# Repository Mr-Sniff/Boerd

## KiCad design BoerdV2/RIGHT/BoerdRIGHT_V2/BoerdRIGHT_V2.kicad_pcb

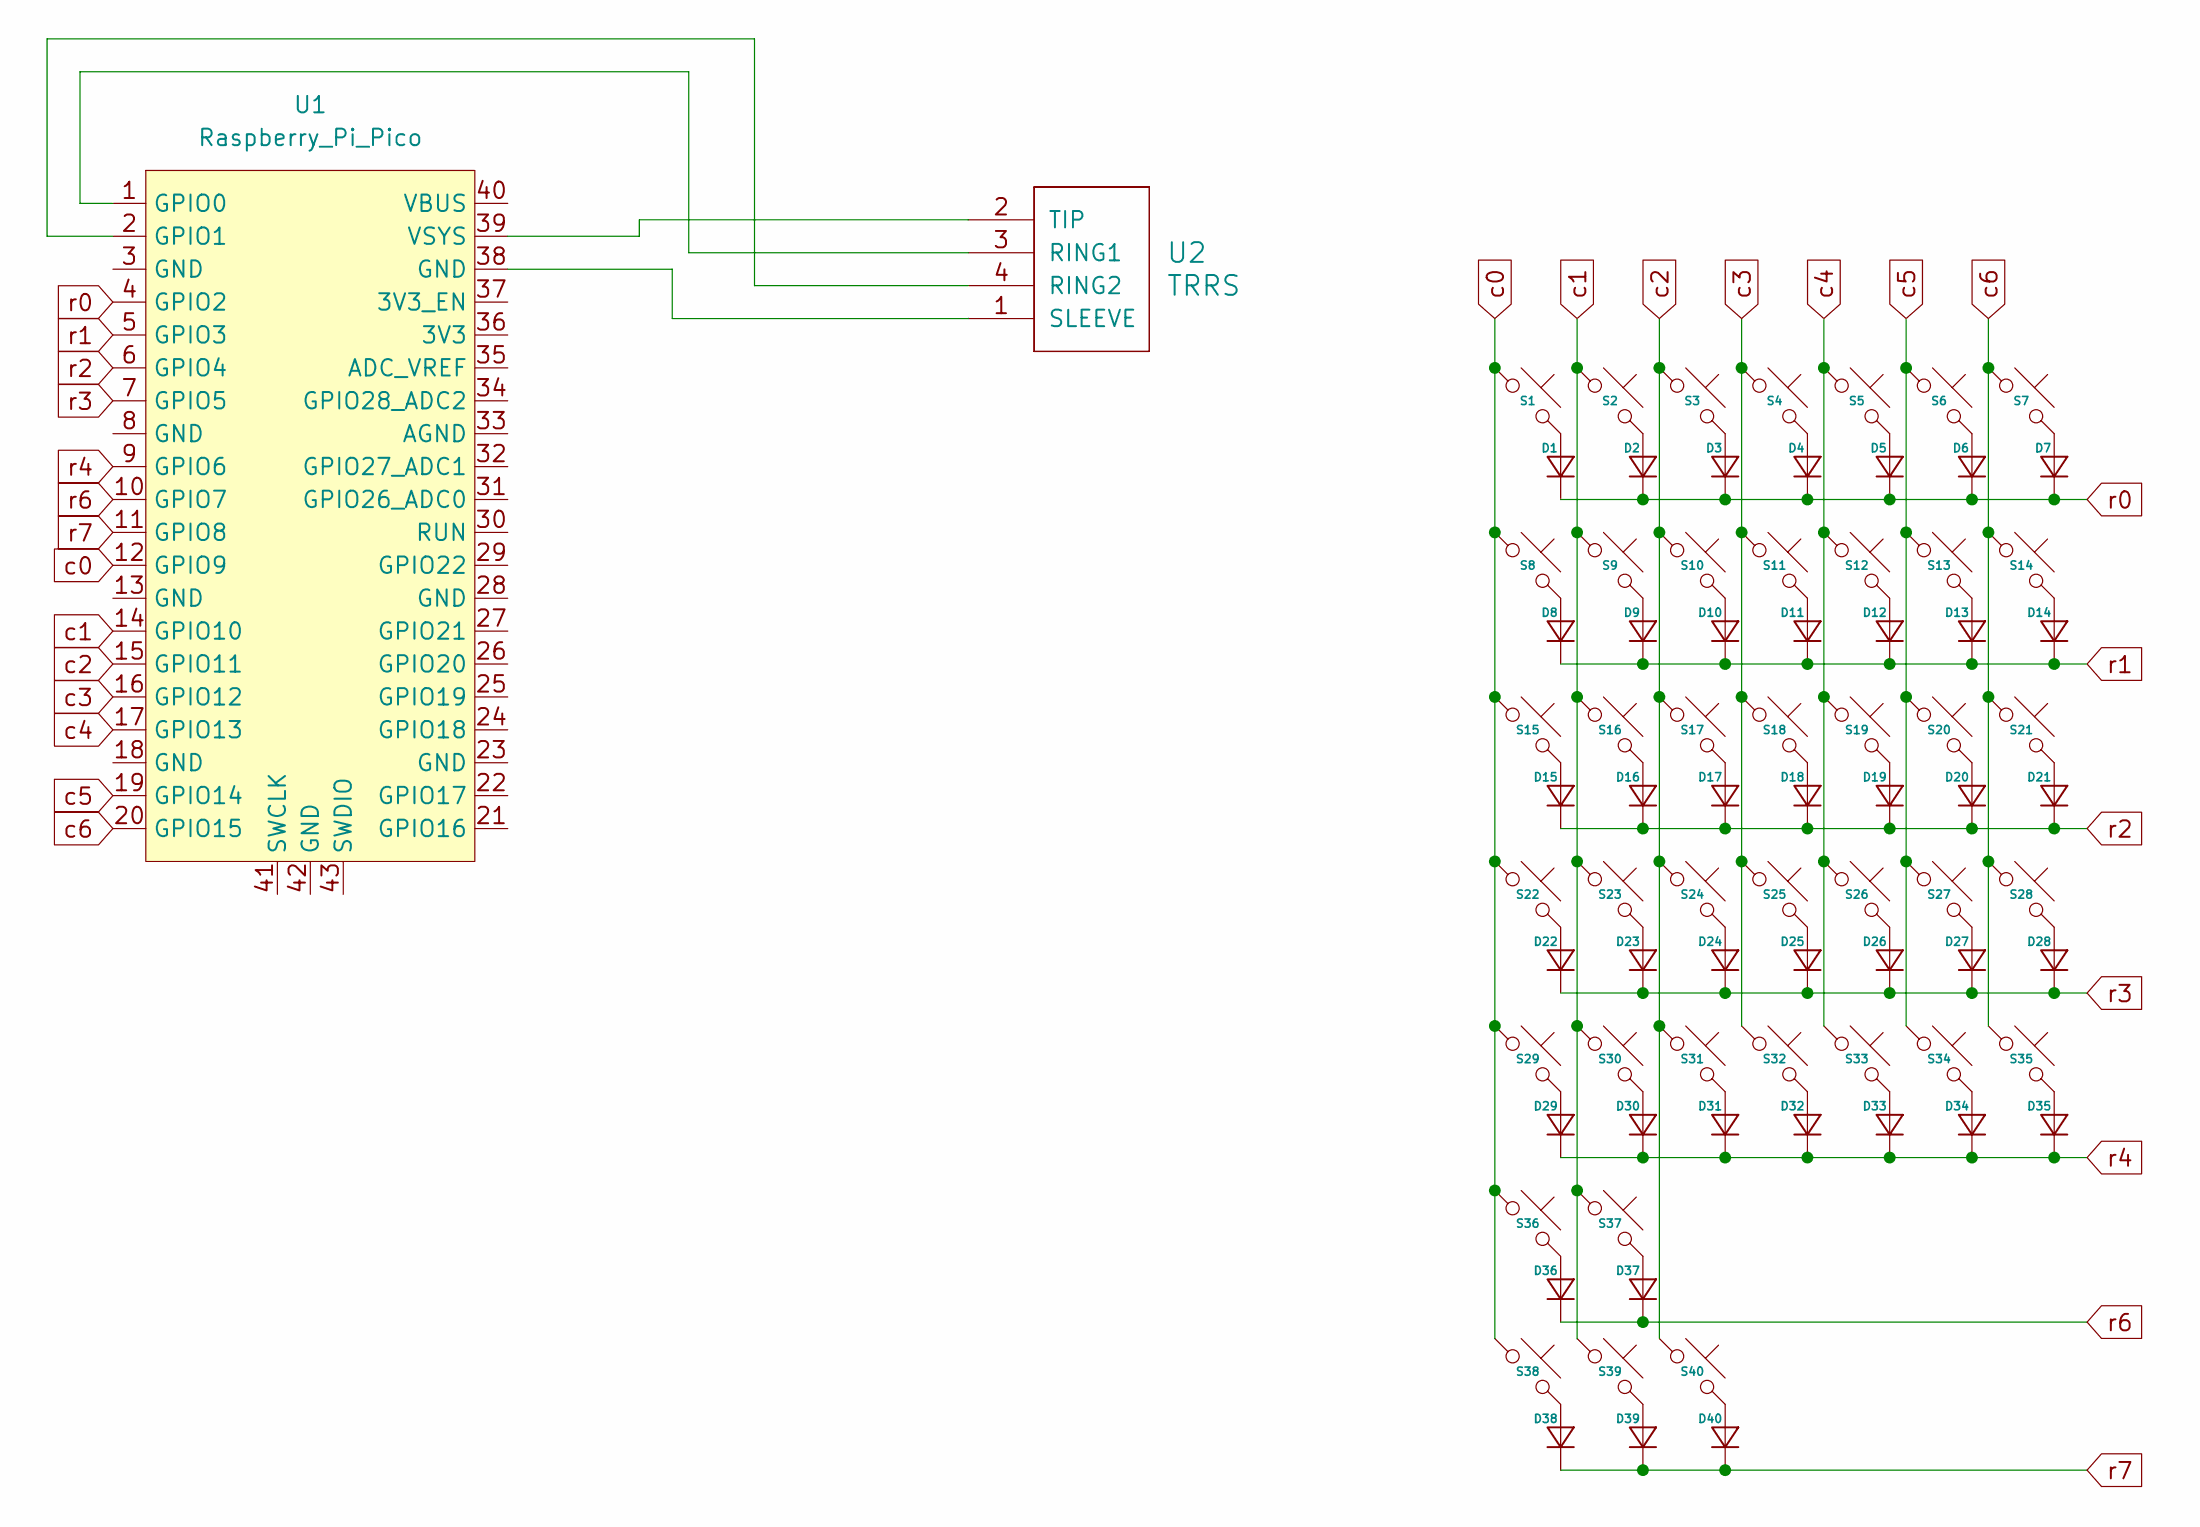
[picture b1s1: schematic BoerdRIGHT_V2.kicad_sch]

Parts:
D1, D2, D3, D4, D5, D6, D7, D8, D9, D10, D11, D12, D13, D14, D15, D16, D17, D18, D19, D20, D21, D22, D23, D24, D25, D26, D27, D28, D29, D30, D31, D32, D33, D34, D35, D36, D37, D38, D39, D40: Diode_DO-35
S1, S2, S3, S4, S5, S6, S8, S9, S10, S11, S12, S13, S15, S16, S17, S18, S19, S20, S22, S23, S24, S25, S26, S27, S29, S30, S31, S32, S33, S34, S36, S37, S38: MX_PCB_1.00u
S7, S14, S21, S28, S35: MX_PCB_1.25u
S39, S40: MX_PCB_1.50u_90deg
U1: Raspberry_Pi_Pico
U2: TRRS; TRRS_PJ-320A

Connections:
unnamed: D1.2 (A), S1.2
unnamed: D2.2 (A), S2.2
unnamed: D3.2 (A), S3.2
unnamed: D4.2 (A), S4.2
unnamed: D5.2 (A), S5.2
unnamed: D6.2 (A), S6.2
unnamed: D7.2 (A), S7.2
unnamed: D8.2 (A), S8.2
unnamed: D9.2 (A), S9.2
unnamed: D10.2 (A), S10.2
unnamed: D11.2 (A), S11.2
unnamed: D12.2 (A), S12.2
unnamed: D13.2 (A), S13.2
unnamed: D14.2 (A), S14.2
unnamed: D15.2 (A), S15.2
unnamed: D16.2 (A), S16.2
unnamed: D17.2 (A), S17.2
unnamed: D18.2 (A), S18.2
unnamed: D19.2 (A), S19.2
unnamed: D20.2 (A), S20.2
unnamed: D21.2 (A), S21.2
unnamed: D22.2 (A), S22.2
unnamed: D23.2 (A), S23.2
unnamed: D24.2 (A), S24.2
unnamed: D25.2 (A), S25.2
unnamed: D26.2 (A), S26.2
unnamed: D27.2 (A), S27.2
unnamed: D28.2 (A), S28.2
unnamed: D29.2 (A), S29.2
unnamed: D30.2 (A), S30.2
unnamed: D31.2 (A), S31.2
unnamed: D32.2 (A), S32.2
unnamed: D33.2 (A), S33.2
unnamed: D34.2 (A), S34.2
unnamed: D35.2 (A), S35.2
unnamed: D36.2 (A), S36.2
unnamed: D37.2 (A), S37.2
unnamed: D38.2 (A), S38.2
unnamed: D39.2 (A), S39.2
unnamed: D40.2 (A), S40.2
unnamed: U1.1 (GPIO0), U2.3 (RING1)
unnamed: U1.2 (GPIO1), U2.4 (RING2)
unnamed: U1.39 (VSYS), U2.2 (TIP)
unnamed: U1.38 (GND), U2.1 (SLEEVE)
c0: S1.1, S8.1, S15.1, S22.1, S29.1, S36.1, S38.1, U1.12 (GPIO9)
c1: S2.1, S9.1, S16.1, S23.1, S30.1, S37.1, S39.1, U1.14 (GPIO10)
c2: S3.1, S10.1, S17.1, S24.1, S31.1, S40.1, U1.15 (GPIO11)
c3: S4.1, S11.1, S18.1, S25.1, S32.1, U1.16 (GPIO12)
c4: S5.1, S12.1, S19.1, S26.1, S33.1, U1.17 (GPIO13)
c5: S6.1, S13.1, S20.1, S27.1, S34.1, U1.19 (GPIO14)
c6: S7.1, S14.1, S21.1, S28.1, S35.1, U1.20 (GPIO15)
r0: D1.1 (K), D2.1 (K), D3.1 (K), D4.1 (K), D5.1 (K), D6.1 (K), D7.1 (K), U1.4 (GPIO2)
r1: D8.1 (K), D9.1 (K), D10.1 (K), D11.1 (K), D12.1 (K), D13.1 (K), D14.1 (K), U1.5 (GPIO3)
r2: D15.1 (K), D16.1 (K), D17.1 (K), D18.1 (K), D19.1 (K), D20.1 (K), D21.1 (K), U1.6 (GPIO4)
r3: D22.1 (K), D23.1 (K), D24.1 (K), D25.1 (K), D26.1 (K), D27.1 (K), D28.1 (K), U1.7 (GPIO5)
r4: D29.1 (K), D30.1 (K), D31.1 (K), D32.1 (K), D33.1 (K), D34.1 (K), D35.1 (K), U1.9 (GPIO6)
r6: D36.1 (K), D37.1 (K), U1.10 (GPIO7)
r7: D38.1 (K), D39.1 (K), D40.1 (K), U1.11 (GPIO8)

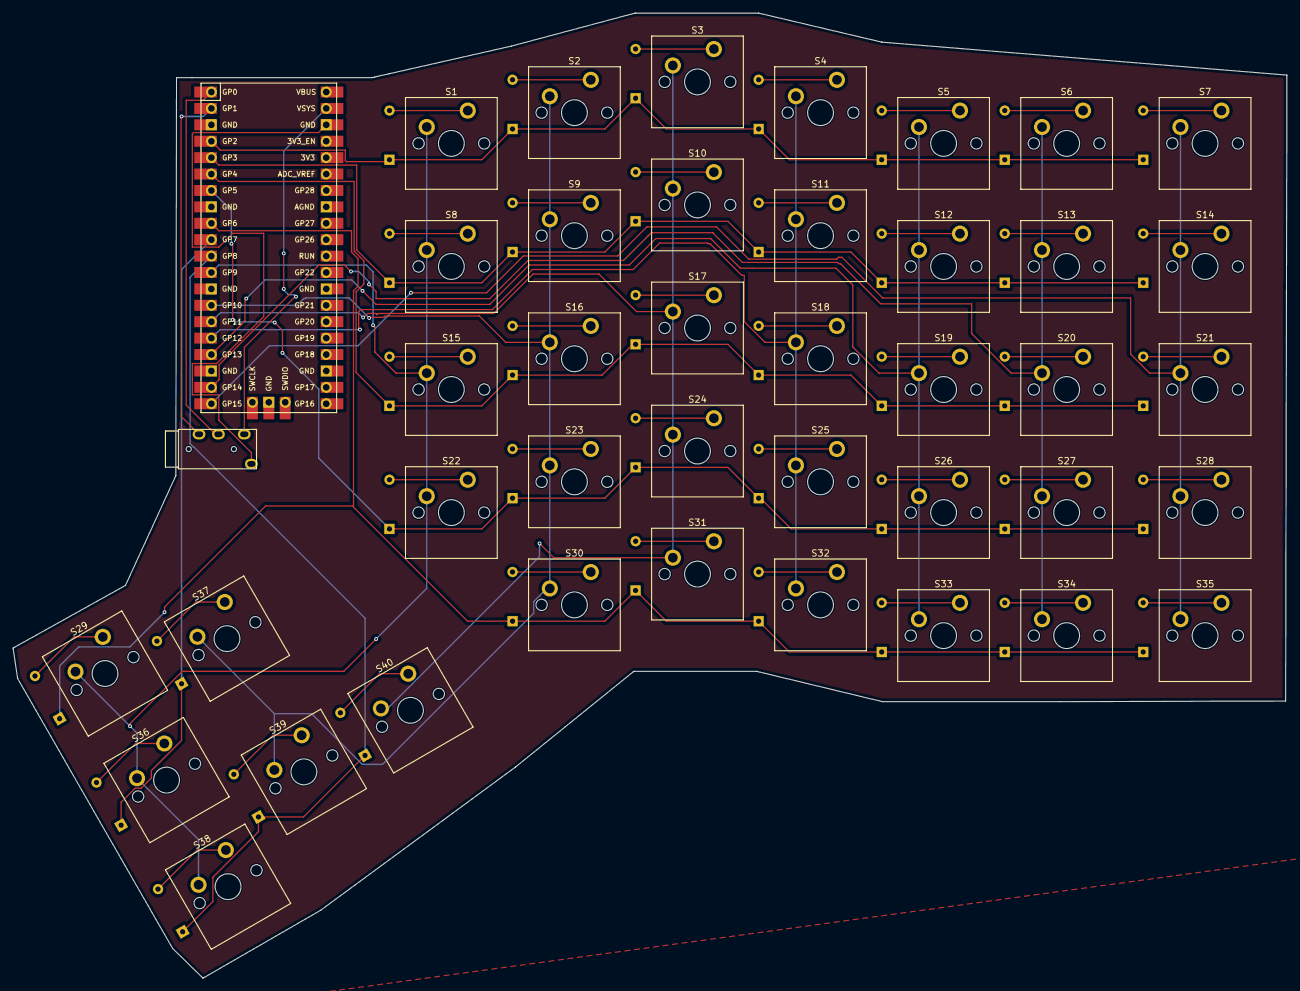
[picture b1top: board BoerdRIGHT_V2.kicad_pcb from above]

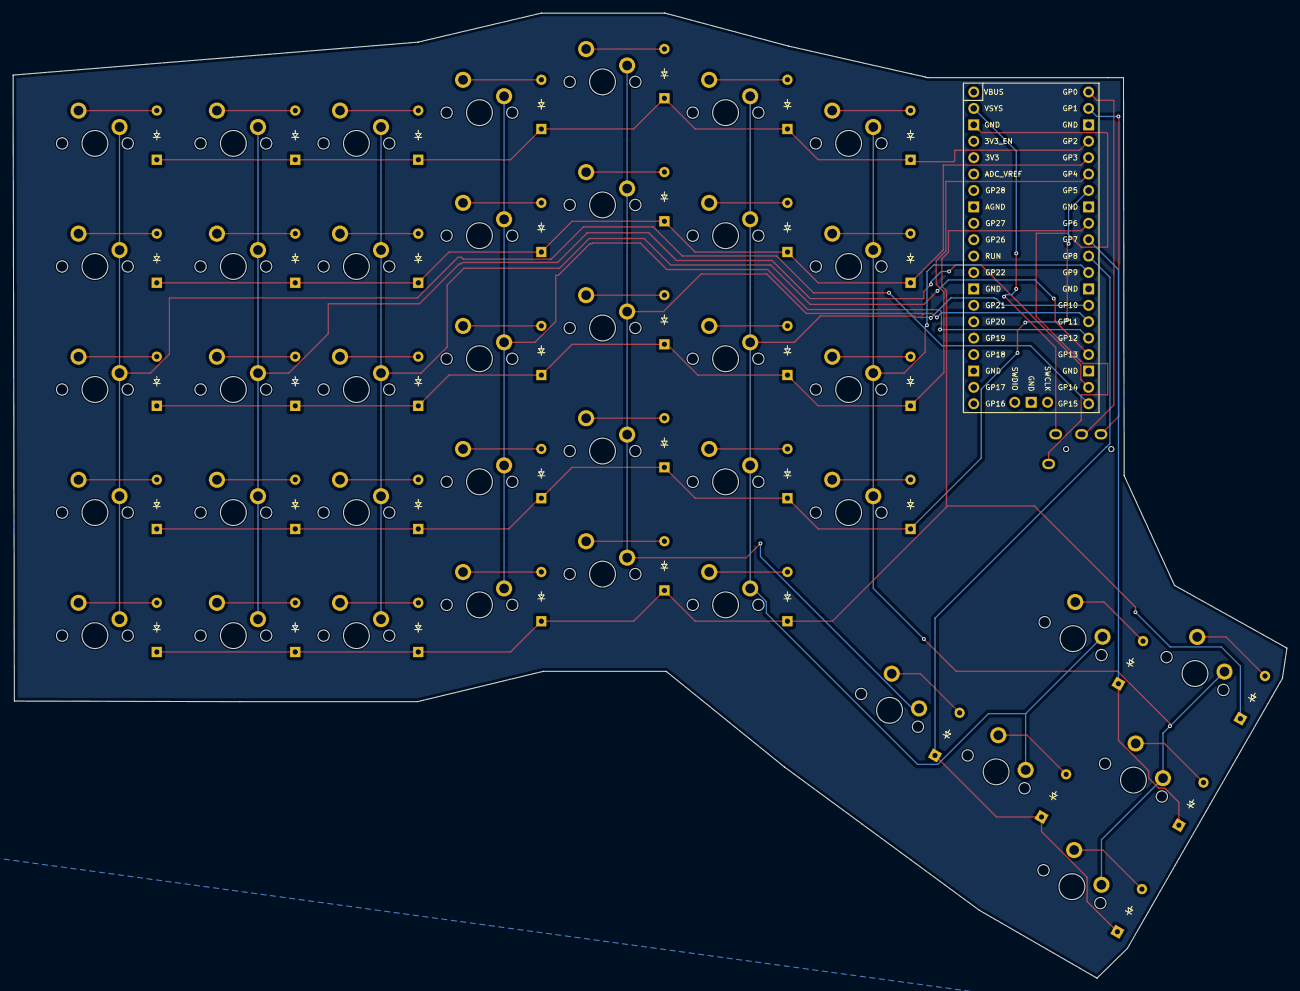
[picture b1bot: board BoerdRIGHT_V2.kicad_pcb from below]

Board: 2 copper layers, 197.2 x 149.4 mm, 82 parts (40 on the bottom side), 58 nets.

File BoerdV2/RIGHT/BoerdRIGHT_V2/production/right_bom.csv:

Designator,Footprint,Quantity,Value,LCSC Part #
"D1, D10, D11, D12, D13, D14, D15, D16, D17, D18, D19, D2, D20, D21, D22, D23, D24, D25, D26, D27, D28, D29, D3, D30, D31, D32, D33, D34, D35, D36, D37, D38, D39, D4, D40, D5, D6, D7, D8, D9",Diode_DO-35,40,~,
"S1, S10, S11, S12, S13, S15, S16, S17, S18, S19, S2, S20, S22, S23, S24, S25, S26, S27, S29, S3, S30, S31, S32, S33, S34, S36, S37, S38, S4, S5, S6, S8, S9",MX_PCB_1.00u,33,~,
"S14, S21, S28, S35, S7",MX_PCB_1.25u,5,~,
"S39, S40",MX_PCB_1.50u_90deg,2,~,
U1,Raspberry_Pi_Pico,1,Raspberry_Pi_Pico,
U2,TRRS_PJ-320A,1,TRRS,

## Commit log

2025-11-30 json files
2025-11-30 fkdlsajk
2025-11-30 new json
2025-11-30 bunch of stuff honsestly
2025-12-02 cosostyletest
2025-12-04 kicad start
2025-12-07 ALOT
